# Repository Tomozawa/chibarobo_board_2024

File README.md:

# chiba_robo_board_2024
## 概要
ちばロボ2024に参加する1年生向けの制御基板です。

## 機能一覧
- マイコンボードESP32S2-DevKitM-1で操作可能
- Cytron MD10C向けコントロールピンx5
- 60kgサーボ向けコントロールピン&amp;7.5V/5A高効率電源
- マイコンボード直結GPIOピン
- 12~24VDC/50Aのアクチュエータ電源
- 外付け非常停止スイッチ
- ソフトスタート内蔵

<br>前面

<br>背面

# マイコンボード
本基板はESP32S2-DevKitM-1でアクチュエータ類を操作します。基板上のピンソケットに、シルクに描画されている向きに従ってESP32S2-DevKitM-1を差し込んでください。

各種アクチュエータ/センサとマイコンボードのピンアサインは以下のとおりです。
| ピン | アクチュエータ/センサ | 説明 |
| ----- | ----- | ------ |
| 33 | DCモーター1 | DCモーター1のPWM信号 |
| 34 | DCモーター2 | DCモーター2のPWM信号 |
| 35 | DCモーター3 | DCモーター3のPWM信号 |
| 36 | DCモーター4 | DCモーター4のPWM信号 |
| 37 | DCモーター5 | DCモーター5のPWM信号 |
| 38 | DCモーター1 | DCモーター1のDIR信号 |
| 39 | DCモーター2 | DCモーター2のDIR信号 |
| 40 | DCモーター3 | DCモーター3のDIR信号 |
| 41 | DCモーター4 | DCモーター4のDIR信号 |
| 42 | DCモーター5 | DCモーター5のDIR信号 |
| 18 | サーボモーター1 | サーボモーター1のPWM信号 |
| 19 | サーボモーター2 | サーボモーター2のPWM信号 |
| 20 | サーボモーター3 | サーボモーター3のPWM信号 |
| 21 | サーボモーター4 | サーボモーター4のPWM信号 |
| 26 | サーボモーター5 | サーボモーター5のPWM信号 |
| 16 | 非常停止ボタン | HIGH: 非常停止ボタンが押されて**いない** LOW:非常停止ボタンが押されて**いる** |
| 5V || ロジック電源で動く回路の電源 |
| GND || ロジック電源で動く回路の共通電位 |

16番ピンは、出力モードに**設定しない**でください。非常停止ボタンのオーバーライド機能が無効になったり、非常停止ボタンが扱われた際、リレーが遮断しなくなることがあります。

# Cytron MD10C向けコントロールピン
Cytron製モータードライバ「Cytron MD10C」向けのDIR/PWM/GNDピンを5チャンネル提供します。

DIRピンのHigh/Low切り替えにより、回転方向を変化させます。

PWMピンから出力するPWM信号のデューティー比により、回転速度を変化させます。

GNDピンの電位は、マイコンボードのGNDピンと同電位です。

DIR/PWMピンの出力インピーダンスは2.2kOhm、ロジック電圧は3.3Vです。

# サーボモーター電源/コントロールピン
60kgサーボ向けの7.5V/5A電源および、マイコンボードと絶縁されたPWM信号を提供します。

基板上のピンヘッダに、サーボモーターのQIコネクタを接続するだけで使用できます。

最大5個まで接続可能です(最小動作電流1Aの場合)。

> [!WARNING]
> - 3.3Vや5Vで動作するサーボモーターを接続しないでください。サーボモーターが焼損する可能性があります。
> - DCDCコンバータICの電流制限機能を外しています。出力電流の管理は、使用者の責任です(<span style="color: red;">最大5Aまで<span>)。

> [!NOTE]
> 無負荷時に150mA程度消費しますが、同期型DCDCコンバータの特性であり、故障ではありません。

# マイコンボード直結のGPIOピン
その他のアクチュエータおよびセンサを接続可能なGPIOピンを備えています。また、特定のGPIOピンからは、EMS信号(非常停止ボタンの信号)を取り出すことができます。(EMS信号を除き)出力電圧/電流は、ESP32S2-DevKitM-1の駆動能力に依存します。すなわち、3.3V/&pm;15mAの駆動能力を持ちます。

EMS信号は3.3V出力で、2.2kOhmの出力インピーダンスを持ちます。

# 12~24VDC/50Aのアクチュエータ電源
アクチュエータの動作に必要な電源を供給するための、電源ハブ機能を備えています。12~24VDC/50Aの範囲の直流電流を流すことができます。

# 外付け非常停止スイッチ
外付けの非常停止スイッチ(NO接点)を使うことで、非常時にアクチュエータ電源を遮断します。また、非常停止スイッチが扱われた際は、マイコンボードに信号が送られます。

外付け非常停止スイッチを使用しない場合、OVERRIDEボタンを使用することで、非常停止機能を一時的に無効にできます。

# ソフトスタート内蔵
バッテリーや端子への負荷を軽減するため、簡易的なソフトスタート機能を備えています。この機能は、電源投入から100ms間、アクチュエータ電源の消費電流を500mAに制限します。これは、アクチュエータ電源に2000uFまでの容量性負荷を接続することを可能にします。

# 確認されているバグ
- LEDのフットプリントミス(D0603サイズ(:サークル標準サイズ)のチップLEDを2つつけることで対処可能)

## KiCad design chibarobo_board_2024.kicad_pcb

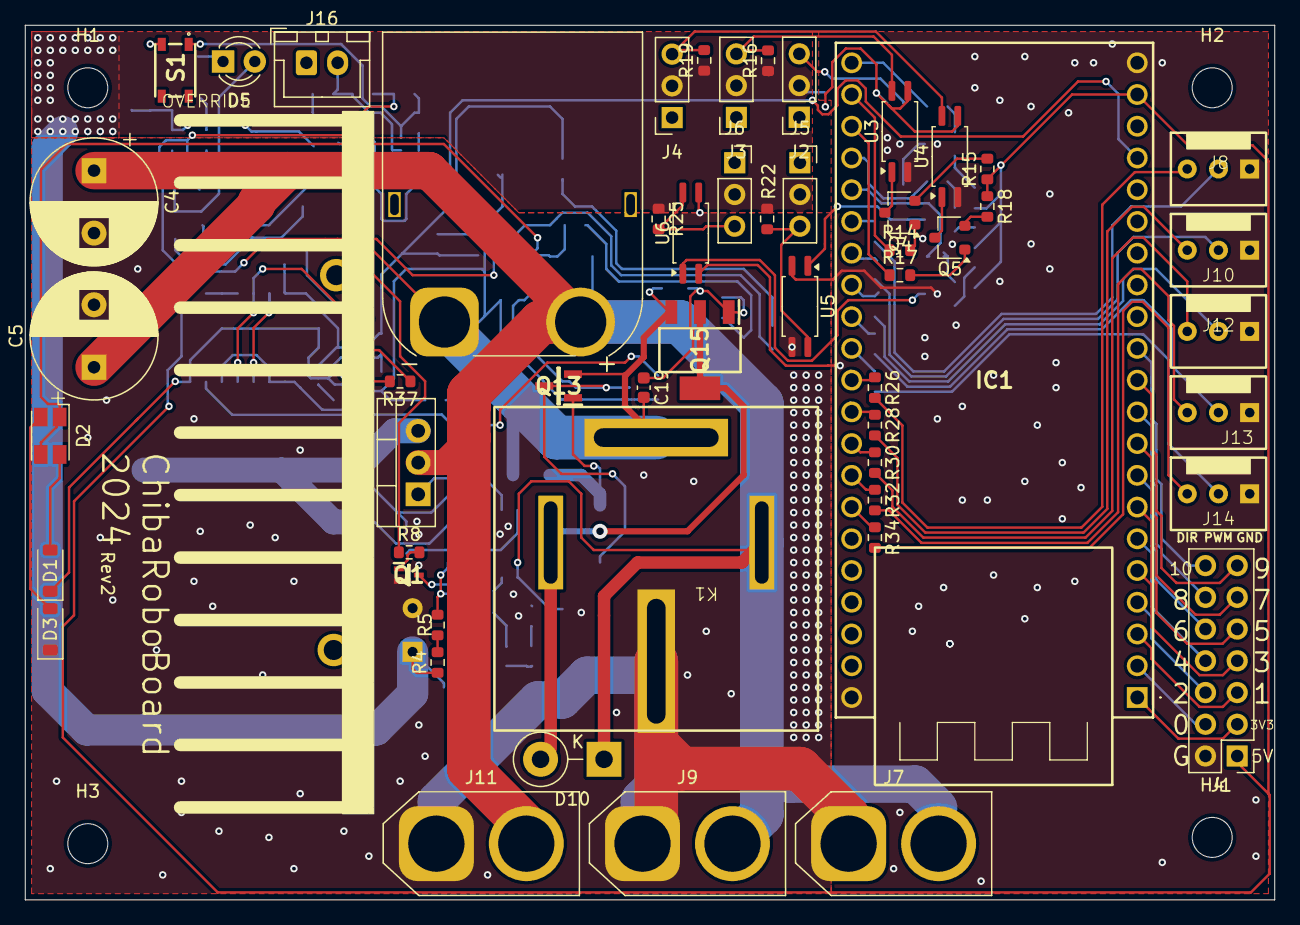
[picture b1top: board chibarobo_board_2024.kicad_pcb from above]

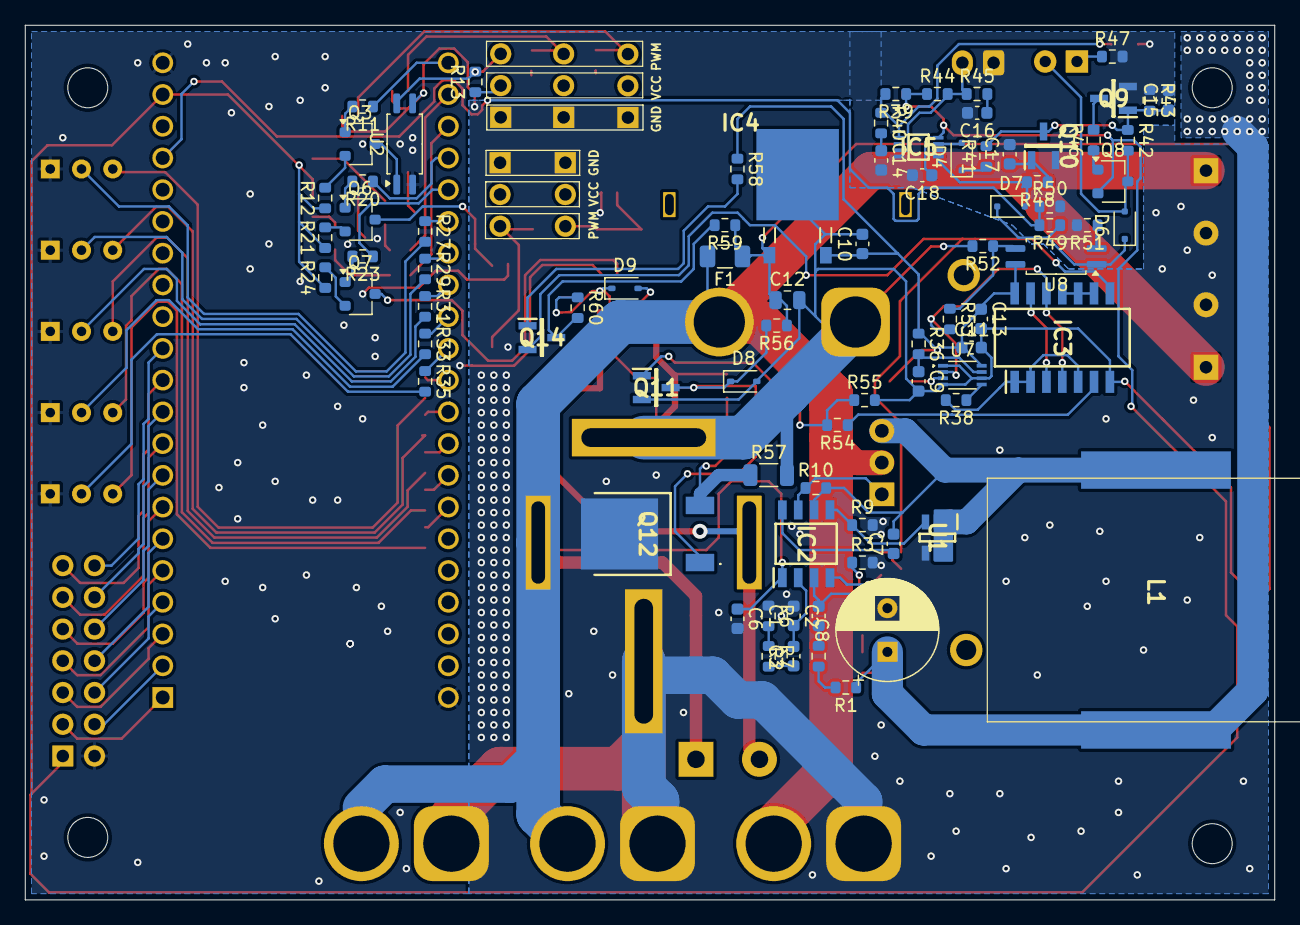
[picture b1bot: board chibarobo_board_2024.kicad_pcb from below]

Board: 2 copper layers, 100.0 x 70.0 mm, 142 parts (83 on the bottom side), 113 nets.

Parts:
C1: 8.2n; C_0603_1608Metric
C2: 18p; C_0603_1608Metric
C3: 3.3n; C_0603_1608Metric
C4, C5: 220u; CP_Radial_D10.0mm_P5.00mm
C6, C7, C10, C11, C13, C14, C16, C17, C18, C19: 100n; C_0603_1608Metric
C8: OS-CON 220uF16V105℃; CP_Radial_D8.0mm_P3.50mm
C9, C15: 1u; C_0603_1608Metric
C12: 10u; C_0805_2012Metric
D1, D3: NSI50010YT1G; D_SOD-123
D2: VLMKG3400; LED_Avago_PLCC4_3.2x2.8mm_CW
D4, D6, D7: D_Schottky; D_SOD-323F
D5: LED; LED_D3.0mm
D8, D9: 12V_Zener; D_SOD-323
D10: D; D_5W_P5.08mm_Vertical_KathodeUp
F1: Fuse; Fuse_1206_3216Metric
H1, H2, H3, H4: MountingHole; MountingHole_3.2mm_M3
HS1: BPUE56-25; BPUE56
IC1: ESP32-S2-DevKitM-1; ESP32S2DevKitM1
IC2: NCP3020ADR2G; SOIC127P600X175-8N
IC3: TC74HC00AF_F_; SOIC127P780X190-14N
IC4: L78M05CDT; TO225P972X240-3N
IC5: TC7W14FK; SOP50P310X90-8N
J1: Conn_01x14_Socket; PinHeader_2x07_P2.54mm_Vertical
J2, J3, J4, J5, J6: Conn_01x03_Socket; PinSocket_1x03_P2.54mm_Vertical
J7, J9, J11: Conn_01x02_Socket; AMASS_XT60-F_1x02_P7.20mm_Vertical
J8, J10, J12, J13, J14: Conn_01x03_Socket; Connector_2510-3P
J15: Conn_01x02_Socket; AMASS_XT90PW-M_1x02_P11.00mm_Horizontal
J16: Conn_01x02_Socket; JST_XH_B2B-XH-A_1x02_P2.50mm_Vertical
K1: V23134J; V23134J1052D642
L1: 60B104C; 60B104C_correct
Q1: NTA7002NT1G; SOT50P160X90-3N
Q2: IRFIZ24NPbF; TO-220-3_Vertical
Q3, Q4, Q5, Q6, Q7, Q8: 2SA1162-GR_F_; SC-59
Q9, Q10, Q11, Q13, Q14: 2SC2712-GR_TE85L,F; SOT95P260X156-3N
Q12: IRFR014TRPBF-BE3; IRFR014TRPBFBE3
Q15: IRFL014TRPBF; SOT230P700X180-4N
R1, R12, R15, R18, R21, R24: 330; R_0603_1608Metric
R2: 18; R_0603_1608Metric
R3: 1.6k; R_0603_1608Metric
R4: 13k; R_0603_1608Metric
R5: 4.7k; R_0603_1608Metric
R6: 3k; R_0603_1608Metric
R7, R9: 56k; R_0603_1608Metric
R8, R52, R58: 10k; R_0603_1608Metric
R10, R55: 1k; R_0603_1608Metric
R11, R14, R17, R20, R23: 16k; R_0603_1608Metric
R13, R16, R19, R22, R25: 560; R_0603_1608Metric
R26, R27, R28, R29, R30, R31, R32, R33, R34, R35, R37, R38, R39, R44, R53, R56: 2.2k; R_0603_1608Metric
R36: 200k; R_0603_1608Metric
R40, R45: 100k; R_0603_1608Metric
R41, R42: 470; R_0603_1608Metric
R43: 100; R_0603_1608Metric
R46: 430; R_0603_1608Metric
R47: 390; R_0603_1608Metric
R48: 4.3k; R_0603_1608Metric
R49: 1.2k; R_0603_1608Metric
R50: 3.3k; R_0603_1608Metric
R51: 360; R_0603_1608Metric
R54: 5.6k; R_0603_1608Metric
R57: 1.3; R_1206_3216Metric
R59: 1.3k; R_0603_1608Metric
R60: 300; R_0603_1608Metric
S1: SKRPACE010; SMT_4.2X3.2_
U1: TSM3446CX6; SOT95P280X95-6N
U2, U3, U4, U5, U6, U8: TLP291; SOIC-4_4.55x2.6mm_P1.27mm
U7: 74LVC1G123; VSSOP-8_2.3x2mm_P0.5mm

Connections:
+3.3V: IC1.J111 (3V3), J1.3
+5V: C18.1, IC1.J130 (5V), IC5.8 (VCC), J1.1, Q8.2, R12.1, R15.1, R18.1, R21.1, R24.1, R39.1, R44.1
+7.5V: C8.1, J2.2, J3.2, J4.2, J5.2, J6.2, L1.2, R1.1, R4.1, R13.1, R16.1, R19.1, R22.1, R25.1
+BATT: C4.1, C5.1, C6.1, D10.1 (K), F1.2, IC2.1 (VCC), J7.2, J9.2, J11.2, J15.2, K1.86, Q2.2 (D)
-BATT: C9.2, C10.2, C11.2, C12.2, C13.2, C19.2, D1.1 (K), D8.2 (A), D9.2 (A), IC3.7 (GND), IC4.2 (GND), J15.1, K1.87, Q11.2 (EMITTER), Q13.2 (EMITTER), Q15.3 (S), R52.2, R55.2, R57.2, U7.1 (~A), U7.4 (GND), U7.6 (Cext)
/ActuatorPowerSupply/COMP: C2.2, C3.2, IC2.2 (COMP)
/ActuatorPowerSupply/FB: C1.2, IC2.3 (FB), R3.1, R5.2
/DCMotor/DIR1: IC1.J321 (38), R26.1
/DCMotor/DIR2: IC1.J320 (39), R28.1
/DCMotor/DIR3: IC1.J319 (40), R30.1
/DCMotor/DIR4: IC1.J318 (41), R32.1
/DCMotor/DIR5: IC1.J317 (42), R34.1
/DCMotor/PWM1: IC1.J326 (33), R27.1
/DCMotor/PWM2: IC1.J325 (34), R29.1
/DCMotor/PWM3: IC1.J324 (35), R31.1
/DCMotor/PWM4: IC1.J323 (36), R33.1
/DCMotor/PWM5: IC1.J322 (37), R35.1
/PowerSupply/EMS/EMBTN: D7.2 (A), IC5.5 (2Y), R48.2
/PowerSupply/EMS/OVERRIDE: D4.2 (A), IC5.7 (1Y)
/PowerSupply/LOGPWR: C10.1, C11.1, C13.1, IC3.14 (VCC), IC4.3 (OUT), R36.1, R37.1, R58.1, U7.8 (VCC), U8.4
/PowerSupply/SAFE_+BATT: C12.1, D2.1 (AR), D2.3 (AG), F1.1, IC4.1 (IN), R56.1, R59.1
/PowerSupply/WMUP: IC3.1 (1A), IC3.2 (1B), IC3.5 (2B), R38.2
/PowerSupply/~EMS: IC3.4 (2A), IC3.12 (4A), R53.2, U7.2 (B)
/PowerSupply/~SS: IC3.6 (2Y), R54.1
/Servo/Servo1: IC1.J331 (18), R11.1
/Servo/Servo2: IC1.J330 (19), R14.1
/Servo/Servo3: IC1.J329 (20), R17.1
/Servo/Servo4: IC1.J328 (21), R20.1
/Servo/Servo5: IC1.J327 (26), R23.1
GND: C14.2, C15.2, C16.2, C17.2, C18.2, IC1.J131 (G_1), IC1.J311 (G_2), IC5.4 (GND), IC5.6 (3A), J1.2, J8.1, J10.1, J12.1, J13.1, J14.1, J16.1, Q9.2 (EMITTER), Q10.2 (EMITTER), R43.1, R47.2, R50.2, R51.2, S1.3, U2.2, U3.2, U4.2, U5.2, U6.2
GNDPWR: C2.1, C4.2, C5.2, C6.2, C8.2, D3.1 (K), J2.1, J3.1, J4.1, J5.1, J6.1, J7.1, J9.1, J11.1, K1.30, Q1.2 (D), Q12.2, R3.2, R6.1, R9.2, U1.4 (SOURCE), U2.3, U3.3, U4.3, U5.3, U6.3
MS: IC3.8 (3Y), Q14.2 (EMITTER), R8.1
unnamed: C1.1, R2.2
unnamed: C3.1, R7.2
unnamed: C14.1, R40.2
unnamed: C16.1, R45.2
unnamed: D1.2 (A), D2.2 (CR)
unnamed: D2.4 (CG), D3.2 (A)
unnamed: D4.1 (K), R41.1
unnamed: D5.2 (A), D6.2 (A), Q8.3, R42.2
unnamed: D5.1 (K), R47.1
unnamed: D6.1 (K), D7.1 (K), R49.1, U8.1
unnamed: D8.1 (K), Q11.3 (COLLECTOR), Q12.1, Q13.3 (COLLECTOR), R56.2
unnamed: C19.1, D9.1 (K), Q15.1 (G), R60.1
unnamed: D10.2 (A), K1.85, Q15.2 (D_1), Q15.4 (D_2)
unnamed: IC1.J112 (0), J1.4
unnamed: IC1.J113 (1), J1.5
unnamed: IC1.J114 (2), J1.6
unnamed: IC1.J115 (3), J1.7
unnamed: IC1.J116 (4), J1.8
unnamed: IC1.J117 (5), J1.9
unnamed: IC1.J118 (6), J1.10
unnamed: IC1.J119 (7), J1.11
unnamed: IC1.J120 (8), J1.12
unnamed: IC1.J121 (9), J1.13
unnamed: IC1.J122 (10), J1.14
unnamed: C7.1, IC2.8 (BST)
unnamed: IC2.4 (GND), Q1.3 (S)
unnamed: IC2.7 (HSDR), Q2.1 (G), R10.1
unnamed: IC2.5 (LSDR), R9.1, U1.3 (GATE)
unnamed: C7.2, IC2.6 (VSW), L1.1, Q2.3 (S), R10.2, U1.1 (DRAIN_1), U1.2 (DRAIN_2), U1.5 (DRAIN_3), U1.6 (DRAIN_4)
unnamed: IC3.3 (1Y), IC3.13 (4B)
unnamed: IC3.9 (3A), IC3.10 (3B), IC3.11 (4Y)
unnamed: IC5.1 (1A), R39.2, R40.1, S1.1
unnamed: IC5.3 (2A), J16.2, R44.2, R45.1
unnamed: J2.3, R13.2, U2.4
unnamed: J3.3, R16.2, U3.4
unnamed: J4.3, R19.2, U4.4
unnamed: J5.3, R22.2, U5.4
unnamed: J6.3, R25.2, U6.4
unnamed: J8.2, R27.2
unnamed: J8.3, R26.2
unnamed: J10.2, R29.2
unnamed: J10.3, R28.2
unnamed: J12.2, R31.2
unnamed: J12.3, R30.2
unnamed: J13.2, R33.2
unnamed: J13.3, R32.2
unnamed: J14.2, R35.2
unnamed: J14.3, R34.2
unnamed: Q1.1 (G), R8.2
unnamed: Q3.1, R11.2
unnamed: Q3.2, R12.2
unnamed: Q3.3, U2.1
unnamed: Q4.1, R14.2
unnamed: Q4.2, R15.2
unnamed: Q4.3, U3.1
unnamed: Q5.1, R17.2
unnamed: Q5.2, R18.2
unnamed: Q5.3, U4.1
unnamed: Q6.1, R20.2
unnamed: Q6.2, R21.2
unnamed: Q6.3, U5.1
unnamed: Q7.1, R23.2
unnamed: Q7.2, R24.2
unnamed: Q7.3, U6.1
unnamed: Q8.1, R46.1
unnamed: Q9.3 (COLLECTOR), R46.2
unnamed: C17.1, Q10.1 (BASE), R48.1
unnamed: C15.1, Q9.1 (BASE), Q10.3 (COLLECTOR), R41.2, R42.1, R43.2
unnamed: Q11.1 (BASE), R54.2, R55.1
unnamed: Q12.3, Q13.1 (BASE), R57.1
unnamed: Q14.1 (BASE), R58.2
unnamed: Q14.3 (COLLECTOR), R59.2, R60.2
unnamed: R1.2, R2.1
unnamed: R4.2, R5.1
unnamed: R6.2, R7.1
unnamed: R51.1, U8.2
unnamed: R52.1, R53.1, U8.3
unnamed: R38.1, U7.5 (Q)
unnamed: C9.1, R36.2, U7.7 (RCext)
unnamed: R37.2, U7.3 (~CLR)
~EMS_{INFO}: IC1.J128 (16), R49.2, R50.1

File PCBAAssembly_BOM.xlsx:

Designator | Comment | Footprint | JLCPCB Parts#
C1 | 8.2n | Capacitor_SMD:C_0603_1608Metric
C2 | 18p | Capacitor_SMD:C_0603_1608Metric
C3 | 3.3n | Capacitor_SMD:C_0603_1608Metric
C6 | 100n | Capacitor_SMD:C_0603_1608Metric
C7 | 100n | Capacitor_SMD:C_0603_1608Metric
C9 | 1u | Capacitor_SMD:C_0603_1608Metric
C10 | 100n | Capacitor_SMD:C_0603_1608Metric
C11 | 100n | Capacitor_SMD:C_0603_1608Metric
C12 | 10u | Capacitor_SMD:C_0805_2012Metric
C13 | 100n | Capacitor_SMD:C_0603_1608Metric
C14 | 100n | Capacitor_SMD:C_0603_1608Metric
C15 | 1u | Capacitor_SMD:C_0603_1608Metric
C16 | 100n | Capacitor_SMD:C_0603_1608Metric
C17 | 100n | Capacitor_SMD:C_0603_1608Metric
C18 | 100n | Capacitor_SMD:C_0603_1608Metric
D4 | D_Schottky | Diode_SMD:D_SOD-323F | C50704
D6 | D_Schottky | Diode_SMD:D_SOD-323F | C50704
D7 | D_Schottky | Diode_SMD:D_SOD-323F | C50704
D8 | 12V_Zener | Diode_SMD:D_SOD-323 | C19077447
D9 | 12V_Zener | Diode_SMD:D_SOD-323 | C19077447
IC4 | L78M05CDT | SamacSys_Parts:TO225P972X240-3N | C55509
Q3 | 2SA1162-GR_F_ | Package_TO_SOT_SMD:SC-59 | C155455
Q6 | 2SA1162-GR_F_ | Package_TO_SOT_SMD:SC-59 | C155455
Q7 | 2SA1162-GR_F_ | Package_TO_SOT_SMD:SC-59 | C155455
Q8 | 2SA1162-GR_F_ | Package_TO_SOT_SMD:SC-59 | C155455
Q9 | 2SC2712-GR_TE85L,F | SamacSys_Parts:SOT95P260X156-3N | C83447
Q10 | 2SC2712-GR_TE85L,F | SamacSys_Parts:SOT95P260X156-3N | C83447
Q11 | 2SC2712-GR_TE85L,F | SamacSys_Parts:SOT95P260X156-3N | C83447
Q14 | 2SC2712-GR_TE85L,F | SamacSys_Parts:SOT95P260X156-3N | C83447
R1 | 330 | Resistor_SMD:R_0603_1608Metric
R2 | 18 | Resistor_SMD:R_0603_1608Metric
R3 | 1.6k | Resistor_SMD:R_0603_1608Metric
R6 | 3k | Resistor_SMD:R_0603_1608Metric
R7 | 56k | Resistor_SMD:R_0603_1608Metric
R9 | 56k | Resistor_SMD:R_0603_1608Metric
R10 | 1k | Resistor_SMD:R_0603_1608Metric
R11 | 16k | Resistor_SMD:R_0603_1608Metric
R12 | 330 | Resistor_SMD:R_0603_1608Metric
R13 | 560 | Resistor_SMD:R_0603_1608Metric
R20 | 16k | Resistor_SMD:R_0603_1608Metric
R21 | 330 | Resistor_SMD:R_0603_1608Metric
R23 | 16k | Resistor_SMD:R_0603_1608Metric
R24 | 330 | Resistor_SMD:R_0603_1608Metric
R27 | 2.2k | Resistor_SMD:R_0603_1608Metric
R29 | 2.2k | Resistor_SMD:R_0603_1608Metric
R31 | 2.2k | Resistor_SMD:R_0603_1608Metric
R33 | 2.2k | Resistor_SMD:R_0603_1608Metric
R35 | 2.2k | Resistor_SMD:R_0603_1608Metric
R36 | 200k | Resistor_SMD:R_0603_1608Metric
R38 | 2.2k | Resistor_SMD:R_0603_1608Metric
R39 | 2.2k | Resistor_SMD:R_0603_1608Metric
R40 | 100k | Resistor_SMD:R_0603_1608Metric
R41 | 470 | Resistor_SMD:R_0603_1608Metric
R42 | 470 | Resistor_SMD:R_0603_1608Metric
R43 | 100 | Resistor_SMD:R_0603_1608Metric
R44 | 2.2k | Resistor_SMD:R_0603_1608Metric
R45 | 100k | Resistor_SMD:R_0603_1608Metric
R46 | 430 | Resistor_SMD:R_0603_1608Metric
R47 | 390 | Resistor_SMD:R_0603_1608Metric
R48 | 4.3k | Resistor_SMD:R_0603_1608Metric
R49 | 1.2k | Resistor_SMD:R_0603_1608Metric
R50 | 3.3k | Resistor_SMD:R_0603_1608Metric
R51 | 360 | Resistor_SMD:R_0603_1608Metric
R52 | 10k | Resistor_SMD:R_0603_1608Metric
R53 | 2.2k | Resistor_SMD:R_0603_1608Metric
R54 | 5.6k | Resistor_SMD:R_0603_1608Metric
R55 | 1k | Resistor_SMD:R_0603_1608Metric
R56 | 2.2k | Resistor_SMD:R_0603_1608Metric
R58 | 10k | Resistor_SMD:R_0603_1608Metric
R59 | 1.3k | Resistor_SMD:R_0603_1608Metric
R60 | 300 | Resistor_SMD:R_0603_1608Metric
U2 | TLP291 | Package_SO:SOIC-4_4.55x2.6mm_P1.27mm | C5121290
U7 | 74LVC1G123 | Package_SO:VSSOP-8_2.3x2mm_P0.5mm | C77273
U8 | TLP291 | Package_SO:SOIC-4_4.55x2.6mm_P1.27mm | C5121290

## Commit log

2024-08-11 CircuitComplete
2024-08-13 Rev1
2024-08-25 Rev1.1
2024-08-29 Recalculate OTA feedback
2024-08-31 before elimination of J7
2024-08-31 Rev1.2
2024-08-31 Rev2
2024-09-02 Rev2.0
2024-09-02 gaber
2024-09-03 add order information
